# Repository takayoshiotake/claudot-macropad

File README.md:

# Claudot

> *Each thought ends with a dot.*  
> *The dot is a key.*

[![CC BY-SA 4.0][cc-by-sa-shield]][cc-by-sa]

Claudot is an 12-key macropad.

## Layout

Named after the Japanese punctuation mark "。", known as **"句点"** (*ku-ten*, pronounced [koo-ten]) — the Japanese *period* or *full stop*.
The word **"句"** (*ku*) refers to either a phrase or a clause — a unit of meaning.

Just as a sentence ends with a dot,
a thought ends with a key.

## Schematic

This project was designed using KiCad.
All design files (schematic and PCB layout) are available in the `kicad/` directory.

Open the `.kicad_pro` file with KiCad to view or edit the project.

### FFC Connection

J1 (PCB) and J2 (MCU) are connected using a 0.5 mm pitch, 8-circuit FFC cable (e.g., MOLEX 15166 series compatible).

> [!CAUTION]
> The pin numbering is mirrored between J1 and J2 (1 ↔ 8, 2 ↔ 7, 3 ↔ 6, 4 ↔ 5).

### Key Matrix

This keyboard uses a 3-row by 4-column matrix (12 keys total).
Diodes are configured in the `COL2ROW` direction.

```
Column ──|>|── Switch ── Row
      (A)   (K)
```

### Pin Mapping

| Key Matrix | RP2040 |
|---|---|
| COL0 | GP18 |
| COL1 | GP19 |
| COL2 | GP20 |
| COL3 | GP21 |
| ROW0 | GP**23** |
| ROW1 | GP**22** |
| ROW2 | GP24 |

## Vial

Prebuilt firmware: [claudot_vial.uf2](assets/claudot_vial.uf2).

### Build with Docker

Copy the `vial/claudot` directory to `path/to/your/vial-qmk/keyboards/`.

```bash
SKIP_FLASHING_SUPPORT=1 util/docker_build.sh claudot:vial
```

- <https://get.vial.today/docs/porting-to-vial.html>
- <https://docs.qmk.fm/getting_started_docker>

## License

This work is licensed under a
[Creative Commons Attribution-ShareAlike 4.0 International License][cc-by-sa].

[![CC BY-SA 4.0][cc-by-sa-image]][cc-by-sa]

[cc-by-sa]: https://creativecommons.org/licenses/by-sa/4.0/
[cc-by-sa-image]: https://licensebuttons.net/l/by-sa/4.0/88x31.png
[cc-by-sa-shield]: https://img.shields.io/badge/license-CC%20BY--SA%204.0-lightgrey.svg

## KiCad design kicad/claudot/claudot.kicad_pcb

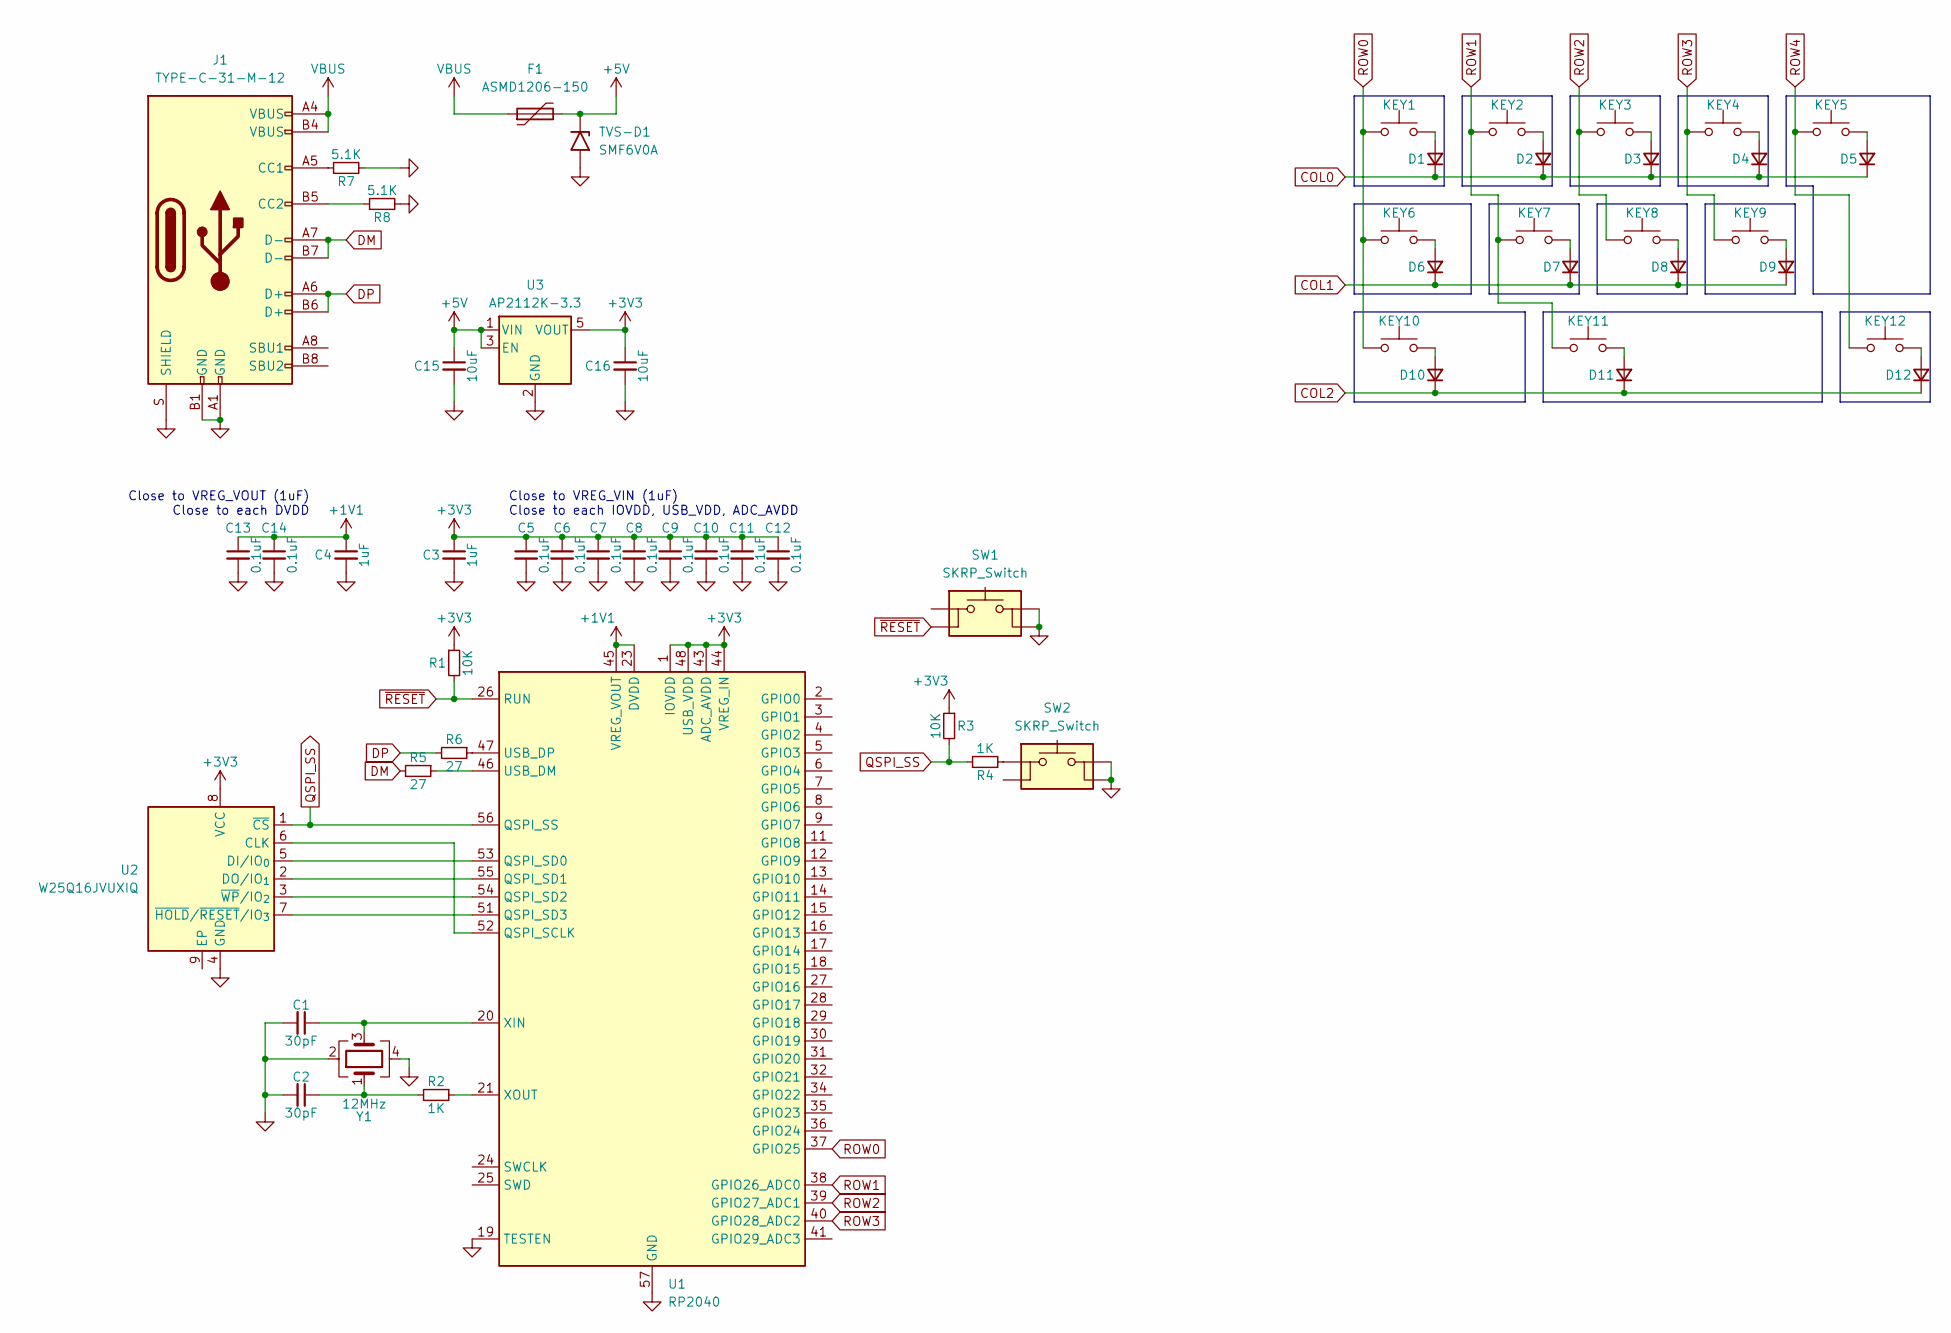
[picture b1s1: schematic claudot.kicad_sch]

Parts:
C1, C2: 30pF; C_0402; LCSC C1570
C3, C4: 1uF; C_0402; LCSC C52923
C5, C6, C7, C8, C9, C10, C11, C12, C13, C14: 0.1uF; C_0402; LCSC C307331
C15, C16: 10uF; C_0402; LCSC C15525
D1, D2, D3, D4, D5, D6, D7, D8, D9, D10, D11, D12: D_Small; SOD323
F1: ASMD1206-150; F_1206; LCSC C135342
J1: TYPE-C-31-M-12; LCSC C165948
KEY1, KEY2, KEY3, KEY4, KEY5, KEY6, KEY7, KEY8, KEY9, KEY10, KEY11, KEY12: SW_Push; CPG151101S11-16
R1, R3: 10K; R_0402; LCSC C25744
R2, R4: 1K; R_0402; LCSC C11702
R5, R6: 27; R_0402; LCSC C352446
R7, R8: 5.1K; R_0402; LCSC C25905
SW1, SW2: SKRP_Switch
TVS-D1: SMF6V0A; SMF6.0A; LCSC C178260
U1: RP2040
U2: W25Q16JVUXIQ
U3: AP2112K-3.3; SOT25
Y1: 12MHz; SMD3225-4P; LCSC C9002

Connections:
+1V1: C4.1, C13.1, C14.1, U1.23 (DVDD), U1.45 (VREG_VOUT), U1.50 (DVDD)
+3V3: C3.1, C5.1, C6.1, C7.1, C8.1, C9.1, C10.1, C11.1, C12.1, C16.1, R1.1, R3.1, U1.1 (IOVDD), U1.10 (IOVDD), U1.22 (IOVDD), U1.33 (IOVDD), U1.42 (IOVDD), U1.43 (ADC_AVDD), U1.44 (VREG_IN), U1.48 (USB_VDD), U1.49 (IOVDD), U2.8 (VCC), U3.5 (VOUT)
+5V: C15.1, F1.2, TVS-D1.1 (A1), U3.1 (VIN), U3.3 (EN)
COL0: D1.1 (K), D2.1 (K), D3.1 (K), D4.1 (K), D5.1 (K)
COL1: D6.1 (K), D7.1 (K), D8.1 (K), D9.1 (K)
COL2: D10.1 (K), D11.1 (K), D12.1 (K)
DM: J1.A7 (D-), J1.B7 (D-), R5.2
DP: J1.A6 (D+), J1.B6 (D+), R6.2
GND: C1.2, C2.2, C3.2, C4.2, C5.2, C6.2, C7.2, C8.2, C9.2, C10.2, C11.2, C12.2, C13.2, C14.2, C15.2, C16.2, J1.A1 (GND), J1.B1 (GND), J1.S (SHIELD), R7.2, R8.2, SW1.3, SW1.4, SW2.3, SW2.4, TVS-D1.2 (A2), U1.19 (TESTEN), U1.57 (GND), U2.4 (GND), U3.2 (GND), Y1.2, Y1.4
unnamed: C2.1, R2.2, Y1.1
unnamed: D1.2 (A), KEY1.2
unnamed: D2.2 (A), KEY2.2
unnamed: D3.2 (A), KEY3.2
unnamed: D4.2 (A), KEY4.2
unnamed: D5.2 (A), KEY5.2
unnamed: D6.2 (A), KEY6.2
unnamed: D7.2 (A), KEY7.2
unnamed: D8.2 (A), KEY8.2
unnamed: D9.2 (A), KEY9.2
unnamed: D10.2 (A), KEY10.2
unnamed: D11.2 (A), KEY11.2
unnamed: D12.2 (A), KEY12.2
unnamed: J1.A5 (CC1), R7.1
unnamed: J1.B5 (CC2), R8.1
unnamed: R4.2, SW2.1
unnamed: U1.52 (QSPI_SCLK), U2.6 (CLK)
unnamed: U1.53 (QSPI_SD0), U2.5 (DI/IO_{0})
unnamed: U1.55 (QSPI_SD1), U2.2 (DO/IO_{1})
unnamed: U1.54 (QSPI_SD2), U2.3 (~WP/IO_{2})
unnamed: U1.51 (QSPI_SD3), U2.7 (~HOLD/~RESET/IO_{3})
unnamed: R5.1, U1.46 (USB_DM)
unnamed: R6.1, U1.47 (USB_DP)
unnamed: C1.1, U1.20 (XIN), Y1.3
unnamed: R2.1, U1.21 (XOUT)
QSPI_SS: R3.2, R4.1, U1.56 (QSPI_SS), U2.1 (~CS)
ROW0: KEY1.1, KEY6.1, KEY10.1, U1.37 (GPIO25)
ROW1: KEY2.1, KEY7.1, KEY11.1, U1.38 (GPIO26_ADC0)
ROW2: KEY3.1, KEY8.1, U1.39 (GPIO27_ADC1)
ROW3: KEY4.1, KEY9.1, U1.40 (GPIO28_ADC2)
ROW4: KEY5.1, KEY12.1
VBUS: F1.1, J1.A4 (VBUS), J1.B4 (VBUS)
~RESET: R1.2, SW1.2 (r), U1.26 (RUN)

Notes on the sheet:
Close to VREG_VIN (1uF) Close to each IOVDD, USB_VDD, ADC_AVDD
Close to VREG_VOUT (1uF) Close to each DVDD

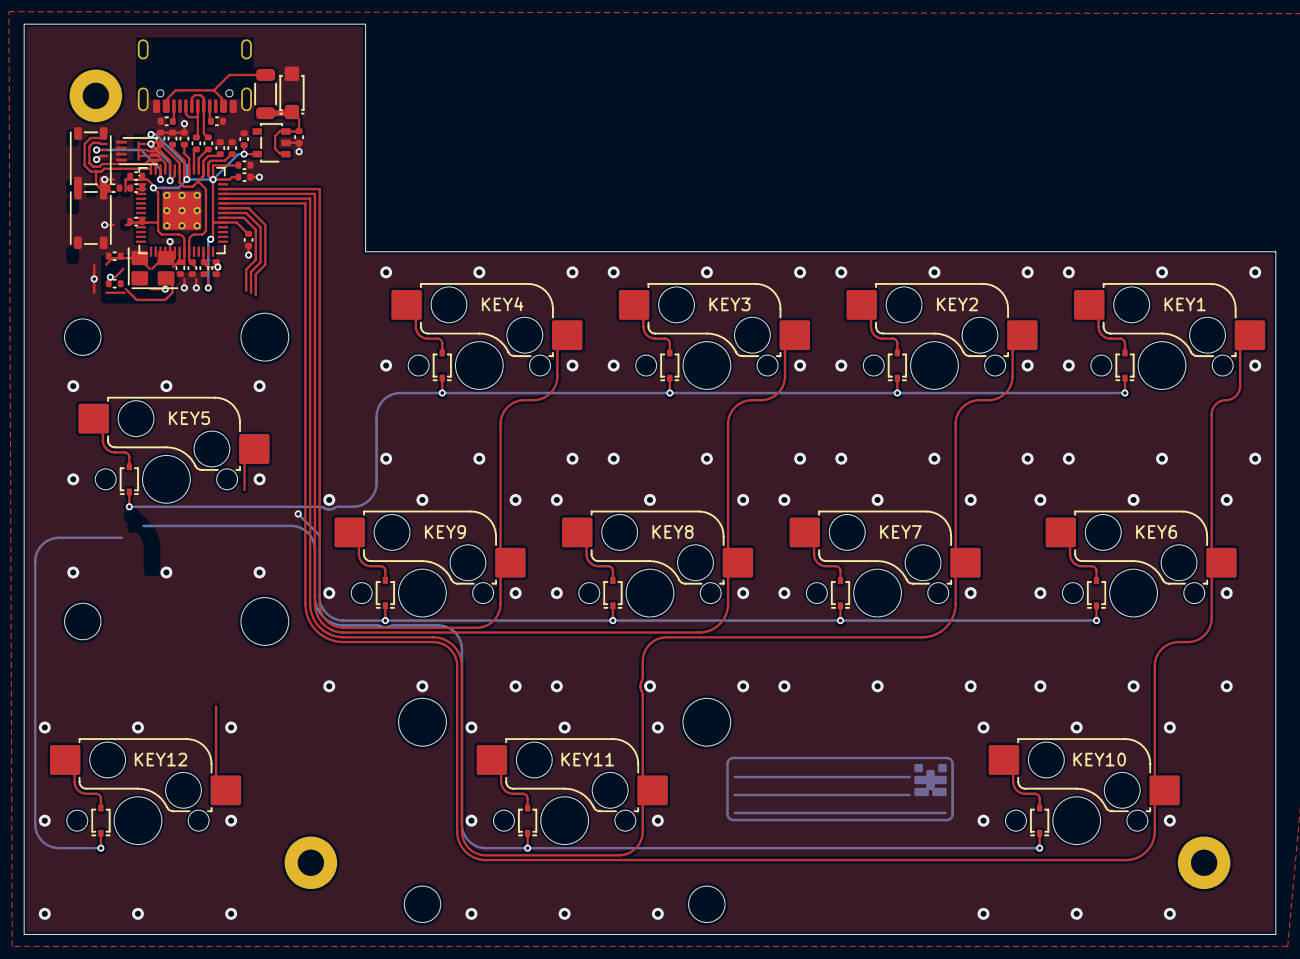
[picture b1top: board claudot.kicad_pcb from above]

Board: 2 copper layers, 104.8 x 76.2 mm, 57 parts (0 on the bottom side), 42 nets.

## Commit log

2025-08-02 Add README with concept
2025-08-10 Add image
2025-08-14 Add initial KiCad project for Claudot
2025-08-14 Add footprint for CPG151101S11-16
2025-08-14 Update CPG151101S11-16 metadata
2025-08-14 Add footprint for SOD323
2025-08-14 Change pad shape to roundrect
2025-08-14 Add footprint for RP2040
2025-08-14 Update RP2040 metadata
2025-08-14 Add footprint for W25Q16JVUXIQ
2025-08-14 Add footprint for SOT25
2025-08-14 Update courtyard
2025-08-15 Update W25Q16JVUXIQ metadata
2025-08-15 Add 3d model for CPG151101S11-16
2025-08-15 Place switches and diodes (no routing)
2025-08-15 Place stabilizers and holes for mounting
2025-08-15 Place ICs and rotary encoder
2025-08-15 Update schematic and pcb
2025-08-16 Reroute traces around U3
2025-08-18 Change J1 footprint
2025-08-19 Fix: restore missing hole
2025-08-27 Fix description
2025-08-27 Add USB-C connector
2025-09-08 Update routes on pcb
2025-09-09 Fix footprint for CPG151101S11-16 and update routes
2025-09-12 Update pcb
2025-09-13 Move kicad library
2025-09-13 Separate PCB designs into individual KiCad projects
2025-09-13 Cleanup traces
2025-09-13 Adjust traces
2025-09-14 Update MCU pcb
2026-01-17 concept: remove rotary encoder, return to key-based design
2026-01-17 kicad: replace rotary encoder with key
2026-01-17 kicad: update Claudot_MCU.kicad_pcb
2026-02-07 chore: initialize claudot project with pcb rules
2026-02-07 chore: import kicad library tables
2026-02-07 feat: add integrated schematic for claudot
2026-02-08 fix: correct row/column net labels
2026-02-08 feat: finalize Claudot_PCB
2026-02-08 feat: finalize Claudot_PCB and Claudot_MCU
2026-02-08 chore: complete LCSC part numbers for Claudot_MCU
2026-02-08 chore: complete LCSC part numbers
2026-02-11 refactor: round pcb corners and adjust silkscreen branding placement
2026-02-13 Add script to export latest edited KiCad deliverables
2026-03-01 Remove unused code
2026-03-01 Add prebuilt firmware
2026-03-02 Add 3d models
2026-03-08 Add housing model
2026-03-15 Add 3D parts
2026-03-15 Add metal sheet housing
2026-04-06 Add yuzukeycaps design
2026-04-06 Change color
2026-04-06 Add size info
